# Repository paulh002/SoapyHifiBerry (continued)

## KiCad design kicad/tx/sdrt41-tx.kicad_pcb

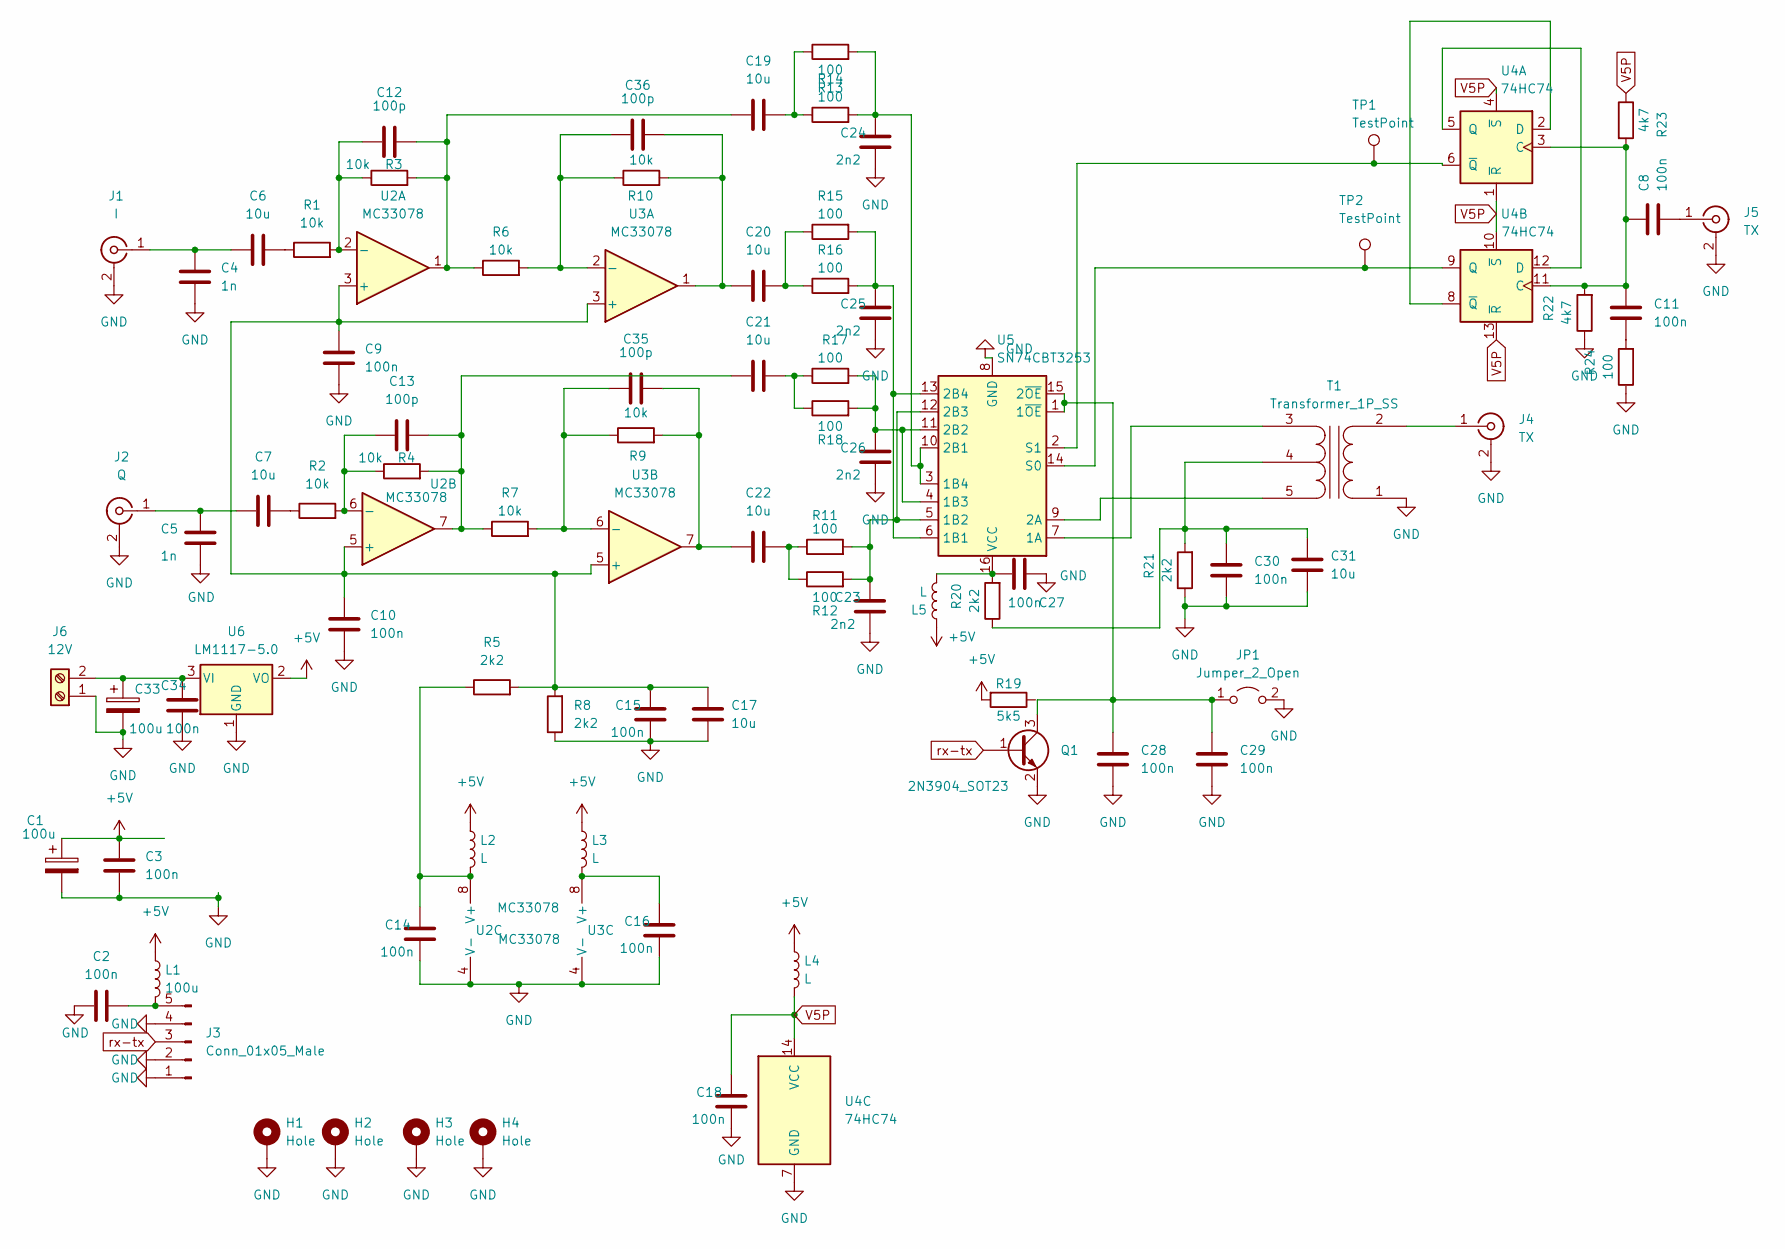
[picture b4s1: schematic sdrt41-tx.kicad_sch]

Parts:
C1, C33: 100u; C_Radial_D5.0mm_H7.0mm_P2.00mm
C2, C3, C8, C9, C10, C11, C14, C15, C16, C18, C27, C28, C29, C30, C34: 100n; C_0805_2012Metric
C4, C5: 1n; C_0805_2012Metric
C6, C7, C17, C19, C20, C21, C22, C31: 10u; C_1206_3216Metric
C12, C13, C35, C36: 100p; C_0805_2012Metric
C23, C24, C25, C26: 2n2; C_0805_2012Metric
H1, H2, H3, H4: Hole; MountingHole_3.2mm_M3_Pad_Via
J1: I; SMA_Amphenol_132134_Vertical
J2: Q; SMA_Amphenol_132134_Vertical
J3: Conn_01x05_Male; PinHeader_1x05_P2.54mm_Vertical
J4, J5: TX; SMA_Amphenol_132134_Vertical
J6: 12V; TerminalBlock_MetzConnect_Type011_RT05502HBWC_1x02_P5.00mm_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
JP1: Jumper_2_Open; SolderJumper-2_P1.3mm_Open_Pad1.0x1.5mm
L1: 100u; L_Axial_L7.0mm_D3.3mm_P5.08mm_Vertical_Fastron_MICC
L2, L3, L4, L5: L; L_0603_1608Metric
Q1: 2N3904_SOT23; SOT-23
R1, R2, R3, R4, R6, R7, R9, R10: 10k; R_0805_2012Metric
R5, R8, R20, R21: 2k2; R_0805_2012Metric
R11, R12, R13, R14, R15, R16, R17, R18, R24: 100; R_0805_2012Metric
R19: 5k5; R_0805_2012Metric
R22, R23: 4k7; R_0805_2012Metric
T1: Transformer_1P_SS; Transformer_Toroid_Horizontal_D12.5mm_Amidon-T44
TP1, TP2: TestPoint; TestPoint_Pad_D1.0mm
U2, U3: MC33078; SO-8_3.9x4.9mm_P1.27mm
U4: 74HC74; SO-14_3.9x8.65mm_P1.27mm
U5: SN74CBT3253; TSSOP-16_4.4x5mm_P0.65mm
U6: LM1117-5.0; SOT-223-3_TabPin2

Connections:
+5V: C1.1, C3.2, L1.1, L2.1, L3.1, L4.1, L5.1, R19.2, U6.2 (VO)
GND: C1.2, C2.2, C3.1, C4.1, C5.1, C9.1, C10.1, C14.1, C15.1, C16.1, C17.1, C18.1, C23.1, C24.1, C25.1, C26.1, C27.1, C28.1, C29.1, C30.1, C31.1, C33.2, C34.1, H1.1, H2.1, H3.1, H4.1, J1.2 (Ext), J2.2 (Ext), J3.1, J3.2, J3.4, J4.2 (Ext), J5.2 (Ext), J6.1, JP1.2 (B), Q1.2 (E), R8.1, R21.1, R22.1, R24.1, T1.1 (AA), U2.4 (V-), U3.4 (V-), U4.7 (GND), U5.8 (GND), U6.1 (GND)
unnamed: C2.1, J3.5, L1.2
unnamed: C4.2, C6.1, J1.1 (In)
unnamed: C5.2, C7.1, J2.1 (In)
unnamed: C6.2, R1.1
unnamed: C7.2, R2.1
unnamed: C8.1, J5.1 (In)
unnamed: C9.2, C10.2, C15.2, C17.2, R5.2, R8.2, U2.3 (+), U2.5 (+), U3.3 (+), U3.5 (+)
unnamed: C11.1, R24.2
unnamed: C12.1, C19.1, R3.2, R6.1, U2.1
unnamed: C12.2, R1.2, R3.1, U2.2 (-)
unnamed: C13.1, C21.1, R4.2, R7.1, U2.7
unnamed: C13.2, R2.2, R4.1, U2.6 (-)
unnamed: C14.2, L2.2, R5.1, U2.8 (V+)
unnamed: C16.2, L3.2, U3.8 (V+)
unnamed: C19.2, R13.1, R14.1
unnamed: C20.1, C36.1, R10.2, U3.1
unnamed: C20.2, R15.1, R16.1
unnamed: C21.2, R17.1, R18.1
unnamed: C22.1, C35.1, R9.2, U3.7
unnamed: C22.2, R11.1, R12.1
unnamed: C23.2, R11.2, R12.2, U5.5 (1B2), U5.12 (2B3)
unnamed: C24.2, R13.2, R14.2, U5.3 (1B4), U5.10 (2B1)
unnamed: C25.2, R15.2, R16.2, U5.6 (1B1), U5.13 (2B4)
unnamed: C26.2, R17.2, R18.2, U5.4 (1B3), U5.11 (2B2)
unnamed: C27.2, L5.2, R20.2, U5.16 (VCC)
unnamed: C28.2, C29.2, JP1.1 (A), Q1.3 (C), U5.1 (1~OE), U5.15 (2~OE)
unnamed: C30.2, C31.2, R20.1, R21.2, T1.4 (SC)
unnamed: C33.1, C34.2, J6.2, U6.3 (VI)
unnamed: C35.2, R7.2, R9.1, U3.6 (-)
unnamed: C36.2, R6.2, R10.1, U3.2 (-)
unnamed: J4.1 (In), T1.2 (AB)
unnamed: T1.3 (SA), U5.7 (1A)
unnamed: T1.5 (SB), U5.9 (2A)
unnamed: TP1.1, U4.6 (~Q), U5.2 (S1)
unnamed: TP2.1, U4.9 (Q), U5.14 (S0)
unnamed: U4.2 (D), U4.8 (~Q)
unnamed: C8.2, C11.2, R22.2, R23.2, U4.3 (C), U4.11 (C)
unnamed: U4.5 (Q), U4.12 (D)
V5P: C18.2, L4.2, R23.1, U4.1 (~R), U4.4 (~S), U4.10 (~S), U4.13 (~R), U4.14 (VCC)
rx-tx: J3.3, Q1.1 (B)

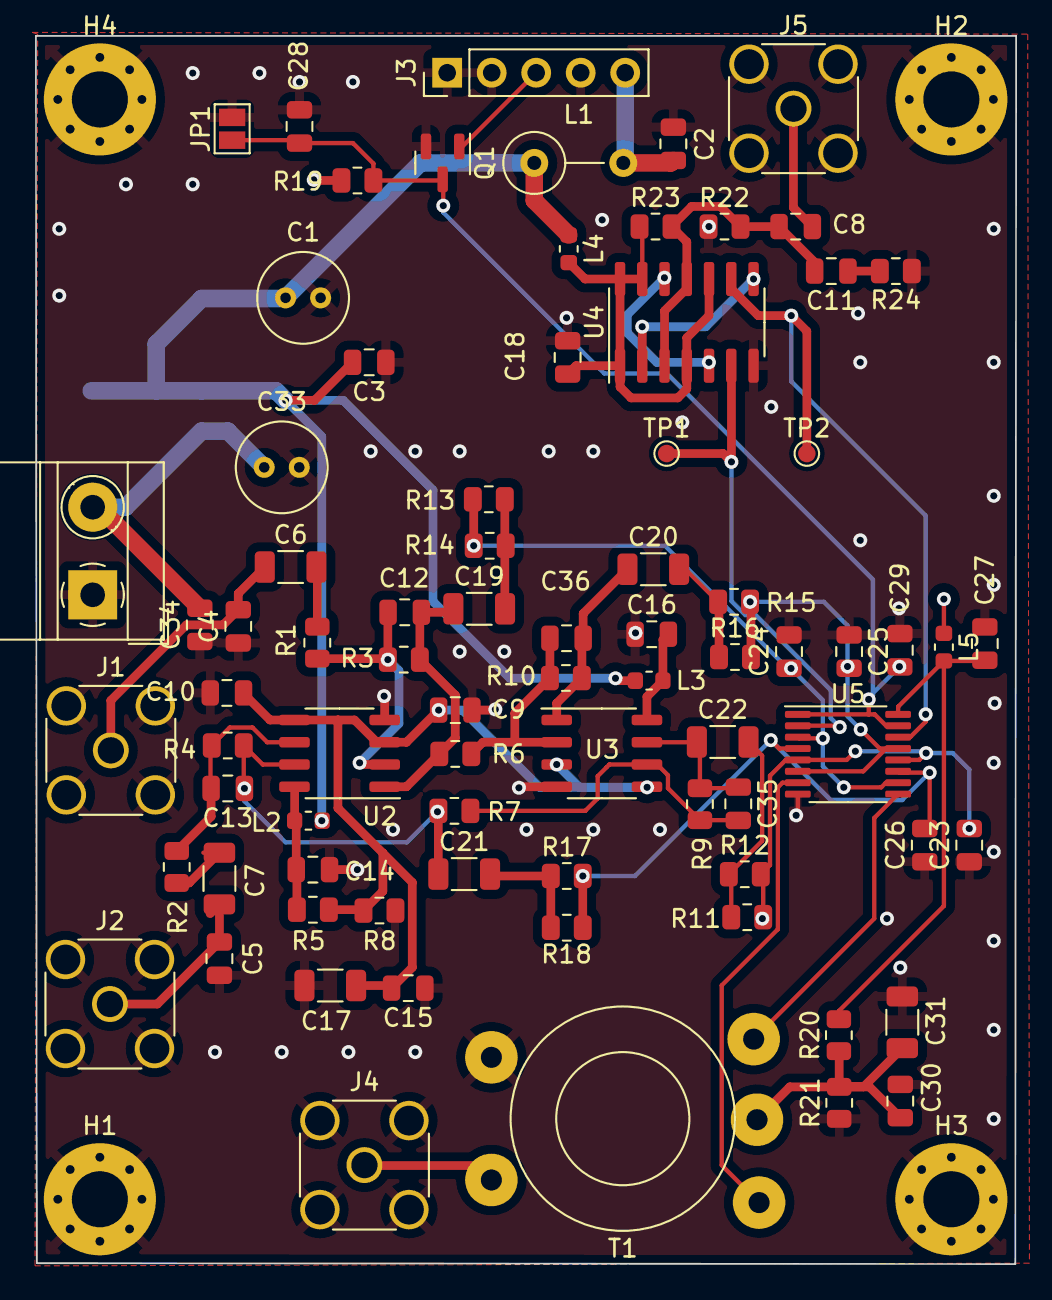
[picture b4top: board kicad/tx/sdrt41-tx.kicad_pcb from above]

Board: 4 copper layers, 56.0 x 70.1 mm, 84 parts (1 on the bottom side), 42 nets.

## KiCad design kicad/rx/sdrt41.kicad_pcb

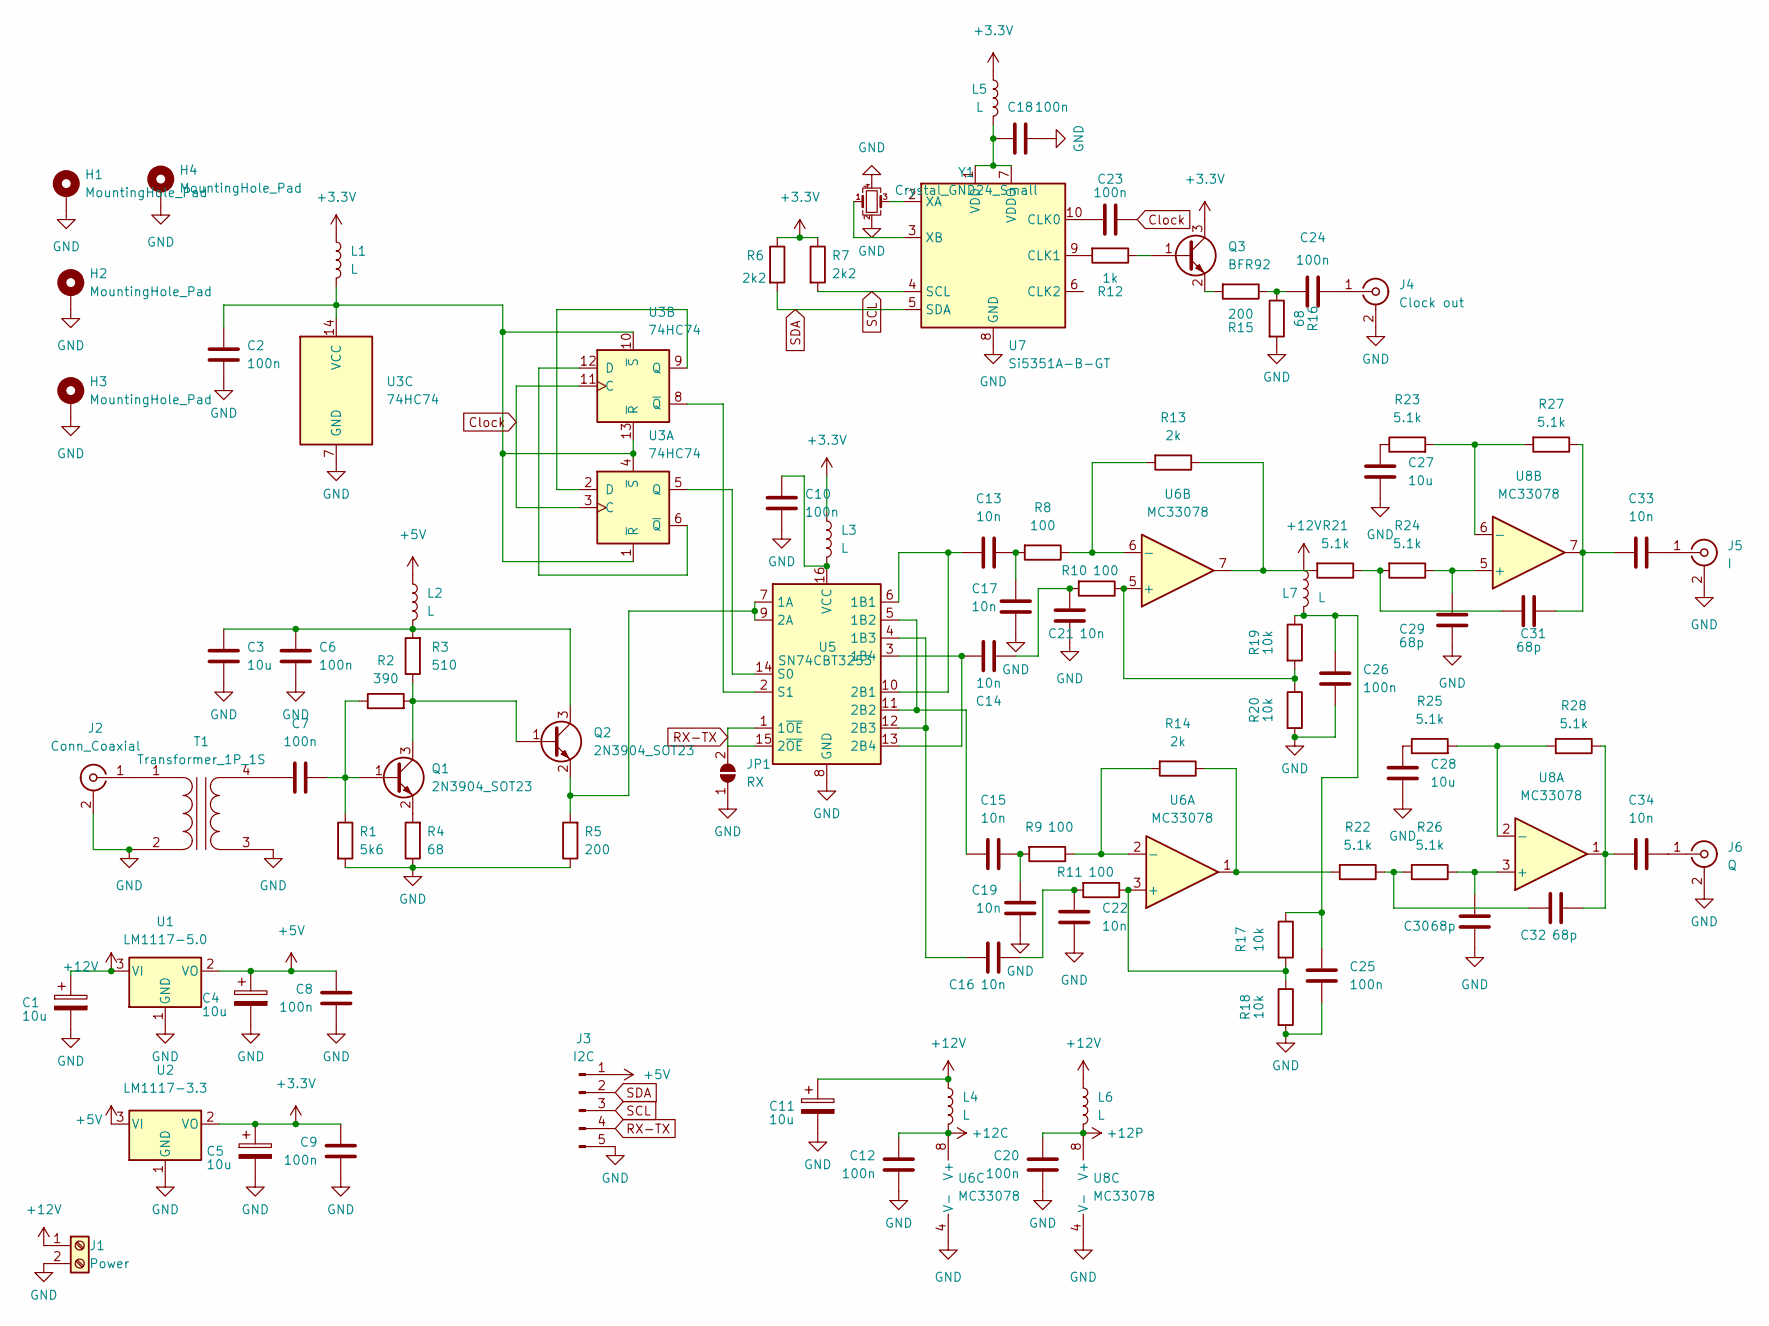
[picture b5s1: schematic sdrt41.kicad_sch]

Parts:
C1, C4: 10u; C_Radial_D10.0mm_H12.5mm_P5.00mm
C2, C6, C7, C8, C9, C10, C12, C18, C20, C23, C24, C25, C26: 100n; C_0805_2012Metric
C3, C11, C27, C28: 10u; C_1206_3216Metric
C5: 10u; C_Radial_D6.3mm_H5.0mm_P2.50mm
C13, C14, C15, C16, C17, C19, C21, C22, C33, C34: 10n; C_0805_2012Metric
C29, C30, C31, C32: 68p; C_0805_2012Metric
H1, H2, H3, H4: MountingHole_Pad; MountingHole_3.2mm_M3_Pad_Via
J1: Power; TerminalBlock_MetzConnect_Type011_RT05502HBWC_1x02_P5.00mm_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
J2: Conn_Coaxial; SMA_Amphenol_132134_Vertical
J3: I2C; PinHeader_1x05_P2.54mm_Vertical
J4: Clock out; SMA_Amphenol_132134_Vertical
J5: I; SMA_Amphenol_132134_Vertical
J6: Q; SMA_Amphenol_132134_Vertical
JP1: RX; SolderJumper-2_P1.3mm_Open_Pad1.0x1.5mm
L1, L2, L3, L4, L5, L6, L7: L; L_0603_1608Metric
Q1, Q2: 2N3904_SOT23; SOT-23
Q3: BFR92; SOT-23
R1: 5k6; R_0805_2012Metric
R2: 390; R_0805_2012Metric
R3: 510; R_0805_2012Metric
R4, R16: 68; R_0805_2012Metric
R5, R15: 200; R_0805_2012Metric
R6, R7: 2k2; R_0805_2012Metric
R8, R9, R10, R11: 100; R_0805_2012Metric
R12: 1k; R_0805_2012Metric
R13, R14: 2k; R_0805_2012Metric
R17, R18, R19, R20: 10k; R_0805_2012Metric
R21, R22, R23, R24, R25, R26, R27, R28: 5.1k; R_0805_2012Metric
T1: Transformer_1P_1S; Transformer_Toroid_Horizontal_D14.0mm_Amidon-T50
U1: LM1117-5.0; SOT-223-3_TabPin2
U2: LM1117-3.3; SOT-223-3_TabPin2
U3: 74HC74; SO-14_3.9x8.65mm_P1.27mm
U5: SN74CBT3253; TSSOP-16_4.4x5mm_P0.65mm
U6, U8: MC33078; SO-8_3.9x4.9mm_P1.27mm
U7: Si5351A-B-GT; MSOP-10_3x3mm_P0.5mm
Y1: Crystal_GND24_Small; Crystal_SMD_3225-4Pin_3.2x2.5mm

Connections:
+3V3: C5.1, C9.2, L1.1, L3.1, L5.1, Q3.3 (C), R6.1, R7.1, U2.2 (VO)
+5V: C4.1, C8.2, J3.1, L2.1, U1.2 (VO), U2.3 (VI)
+12C: C12.2, L4.2, U6.8 (V+)
+12P: C20.2, L6.2, U8.8 (V+)
+12V: C1.1, C11.1, J1.1, L4.1, L6.1, L7.1, U1.3 (VI)
Clock: C23.1, U3.3 (C), U3.11 (C)
GND: C1.2, C2.1, C3.1, C4.2, C5.2, C6.1, C8.1, C9.1, C10.1, C11.2, C12.1, C17.1, C18.1, C19.1, C20.1, C21.1, C22.1, C25.1, C26.1, C27.1, C28.1, C29.1, C30.1, H1.1, H2.1, H3.1, H4.1, J1.2, J2.2 (Ext), J3.5, J4.2 (Ext), J5.2 (Ext), J6.2 (Ext), JP1.1 (A), R1.2, R4.1, R5.1, R16.2, R18.2, R20.2, T1.2 (AB), T1.3 (SA), U1.1 (GND), U2.1 (GND), U3.7 (GND), U5.8 (GND), U6.4 (V-), U7.8 (GND), U8.4 (V-), Y1.2, Y1.4
unnamed: C2.2, L1.2, U3.1 (~R), U3.4 (~S), U3.10 (~S), U3.13 (~R), U3.14 (VCC)
unnamed: C3.2, C6.2, L2.2, Q2.3 (C), R3.2
unnamed: C7.1, T1.4 (SB)
unnamed: C7.2, Q1.1 (B), R1.1, R2.1
unnamed: C10.2, L3.2, U5.16 (VCC)
unnamed: C13.1, C17.2, R8.2
unnamed: C13.2, U5.6 (1B1), U5.10 (2B1)
unnamed: C14.1, C21.2, R10.2
unnamed: C14.2, U5.3 (1B4), U5.13 (2B4)
unnamed: C15.1, C19.2, R9.2
unnamed: C15.2, U5.5 (1B2), U5.11 (2B2)
unnamed: C16.1, C22.2, R11.2
unnamed: C16.2, U5.4 (1B3), U5.12 (2B3)
unnamed: C18.2, L5.2, U7.1 (VDD), U7.7 (VDDO)
unnamed: C23.2, U7.10 (CLK0)
unnamed: C24.1, J4.1 (In)
unnamed: C24.2, R15.1, R16.1
unnamed: C25.2, C26.2, L7.2, R17.1, R19.1
unnamed: C27.2, R23.1
unnamed: C28.2, R25.1
unnamed: C29.2, R24.1, U8.5 (+)
unnamed: C30.2, R26.1, U8.3 (+)
unnamed: C31.1, R21.1, R24.2
unnamed: C31.2, C33.1, R27.1, U8.7
unnamed: C32.1, R22.1, R26.2
unnamed: C32.2, C34.1, R28.1, U8.1
unnamed: C33.2, J5.1 (In)
unnamed: C34.2, J6.1 (In)
unnamed: J2.1 (In), T1.1 (AA)
unnamed: Q1.2 (E), R4.2
unnamed: Q1.3 (C), Q2.1 (B), R2.2, R3.1
unnamed: Q2.2 (E), R5.2, U5.7 (1A), U5.9 (2A)
unnamed: Q3.1 (B), R12.1
unnamed: Q3.2 (E), R15.2
unnamed: R10.1, R19.2, R20.1, U6.5 (+)
unnamed: R11.1, R17.2, R18.1, U6.3 (+)
unnamed: R12.2, U7.9 (CLK1)
unnamed: R13.1, R21.2, U6.7
unnamed: R8.1, R13.2, U6.6 (-)
unnamed: R14.1, R22.2, U6.1
unnamed: R9.1, R14.2, U6.2 (-)
unnamed: R23.2, R27.2, U8.6 (-)
unnamed: R25.2, R28.2, U8.2 (-)
unnamed: U3.2 (D), U3.9 (Q)
unnamed: U3.5 (Q), U5.14 (S0)
unnamed: U3.8 (~Q), U5.2 (S1)
unnamed: U3.6 (~Q), U3.12 (D)
unnamed: U7.2 (XA), Y1.3
unnamed: U7.3 (XB), Y1.1
RX-TX: J3.4, JP1.2 (B), U5.1 (1~OE), U5.15 (2~OE)
SCL: J3.3, R7.2, U7.4 (SCL)
SDA: J3.2, R6.2, U7.5 (SDA)

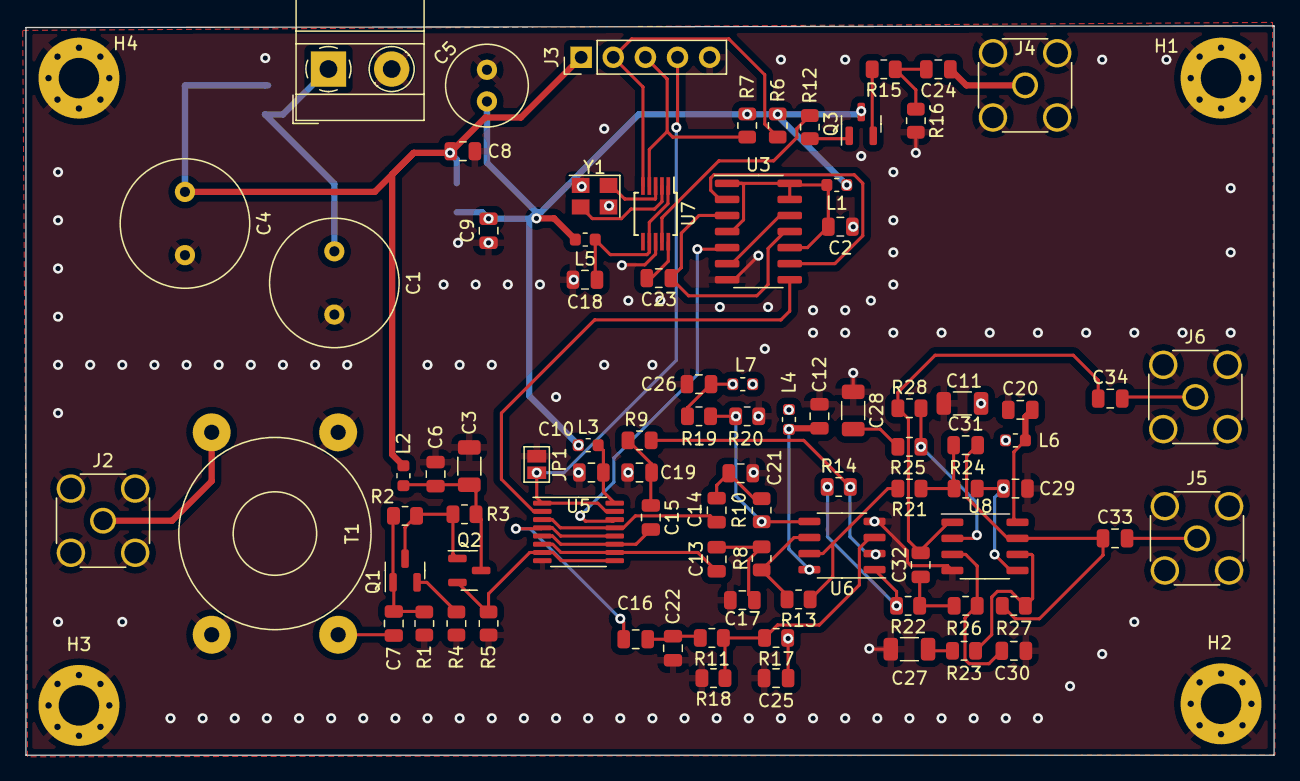
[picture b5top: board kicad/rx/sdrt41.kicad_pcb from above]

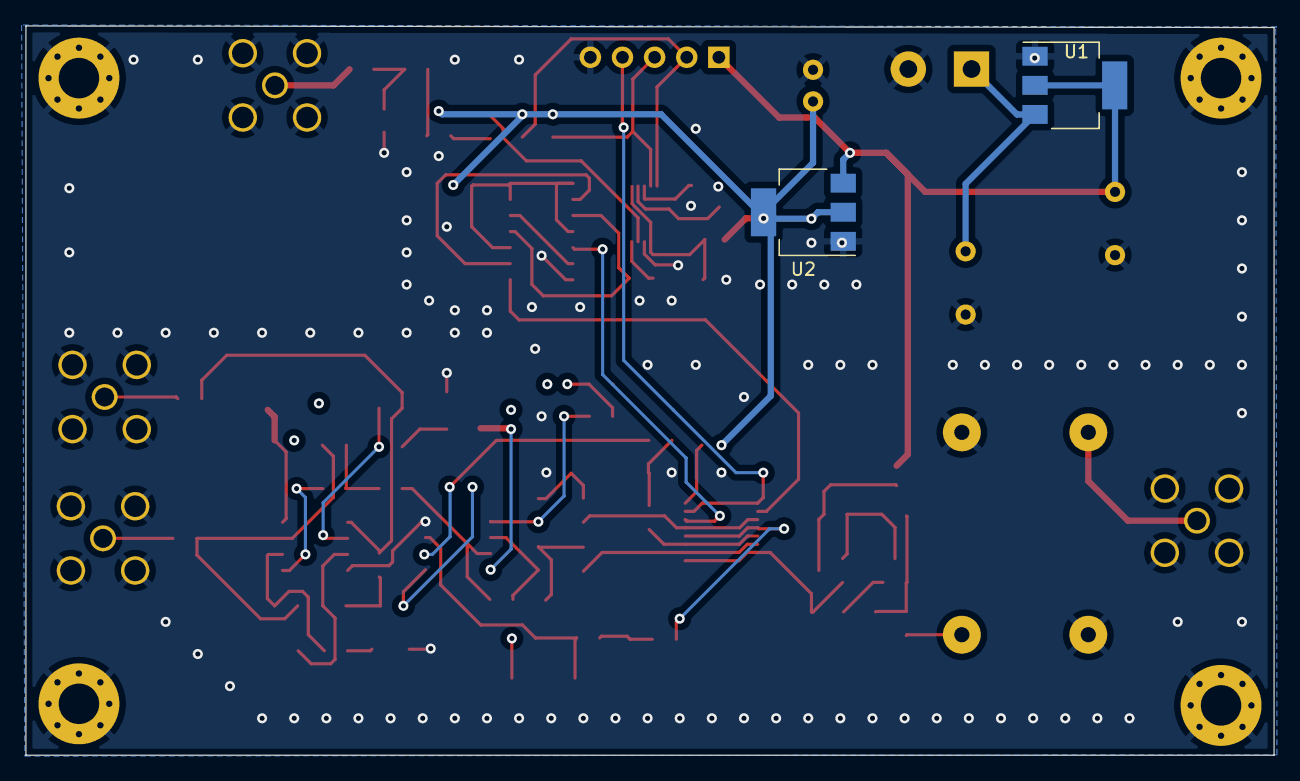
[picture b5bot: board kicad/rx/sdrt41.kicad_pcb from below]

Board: 4 copper layers, 98.7 x 57.7 mm, 92 parts (2 on the bottom side), 59 nets.

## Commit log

2022-06-07 Add .gitignore and .gitattributes.
2022-06-07 Add project files.
2022-06-20 readme
2022-06-20 kicad
2022-06-20 gain
2022-06-21 update gain
2022-06-27 add config file
2022-06-28 update tx
2022-09-18 refactor code due to cmake issues
2022-12-25 fix deactivate stream
2022-12-26 Update TX capacitors
2023-01-03 Delete .visualgdb directory
    remove
2023-01-03 test
2023-01-04 add si5351 drive levels
2023-01-07 add tx gain
2023-01-28 update gain and added differential input setting
2023-05-08 disable spread spectrum
2023-05-20 updare cmake
2023-05-21 update cmake
2023-05-21 add tca9548
2023-05-24 add IQ mode 90 deg phase shift and suppoty fo 2 si5351
2023-05-24 cmake
2023-05-24 update kicad
2023-06-08 fix si5351 i2c handle
2023-06-12 added multiple modes for IQ, fix low frequencies
2023-06-13 fix typo
2023-06-19 fix Single mode
2023-06-20 fix correction
2023-09-01 add 384 DAC samplerate
2023-09-03 update default samplerate
2023-12-01 update version reporting
2023-12-03 support 8 channel si5351
2023-12-03 si5351A GM 8 port support
2023-12-09 fix mode
2023-12-19 update si5351B support
2024-03-02 version 2
2024-03-02 added Si5351A-B-GM version
2024-04-05 Add LTSPice
2024-10-20 fix even divisor
2024-11-07 fix even divisor value, add some ltspice
